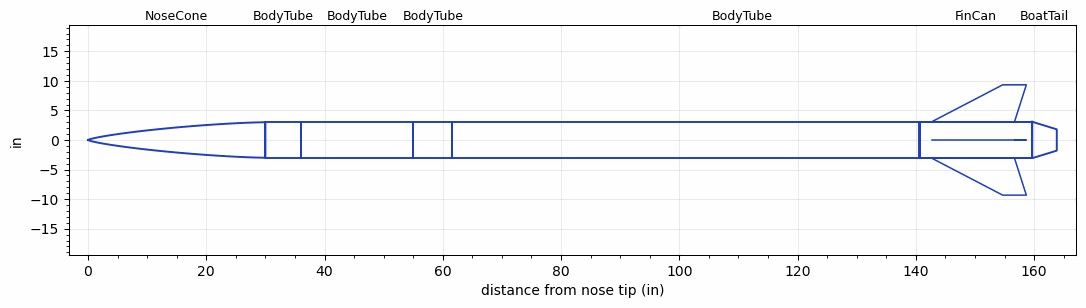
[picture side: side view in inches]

<RASAeroDocument>
 <FileVersion>2</FileVersion>
 <RocketDesign>
  <NoseCone>
   <Length>29.9999</Length>
   <Diameter>6</Diameter>
   <Shape>Von Karman Ogive</Shape>
   <Location>0</Location>
  </NoseCone>
  <BodyTube>
   <Length>6</Length>
   <Diameter>6</Diameter>
   <Location>29.9999</Location>
  </BodyTube>
  <BodyTube>
   <Length>19</Length>
   <Diameter>6</Diameter>
   <Location>35.9999</Location>
  </BodyTube>
  <BodyTube>
   <Length>6.628</Length>
   <Diameter>6</Diameter>
   <Location>54.9999</Location>
  </BodyTube>
  <BodyTube>
   <Length>98.0598</Length>
   <Diameter>6</Diameter>
   <Location>61.6279</Location>
  </BodyTube>
  <FinCan>
   <Length>19</Length>
   <Diameter>6.154</Diameter>
   <InsideDiameter>6</InsideDiameter>
   <Location>159.6877</Location>
   <ShoulderLength>0.1333</ShoulderLength>
   <Offset>-19</Offset>
   <Fin>
    <Count>4</Count>
    <Chord>14</Chord>
    <Span>6.25</Span>
    <SweepDistance>12</SweepDistance>
    <TipChord>4</TipChord>
    <Thickness>0.3</Thickness>
    <LERadius>0.0313</LERadius>
    <Location>17</Location>
    <AirfoilSection>Double Wedge</AirfoilSection>
    <FX1>3.9</FX1>
    <FX3>3.9</FX3>
   </Fin>
  </FinCan>
  <BoatTail>
   <Length>4.15</Length>
   <Diameter>6.154</Diameter>
   <RearDiameter>3.6</RearDiameter>
   <Location>159.6877</Location>
  </BoatTail>
  <Surface>Rough Camouflage Paint</Surface>
  <ModifiedBarrowman>True</ModifiedBarrowman>
  <Turbulence>True</Turbulence>
  <UseBooster1>False</UseBooster1>
  <UseBooster2>False</UseBooster2>
  <Comments>2027 IREC Rocket Design</Comments>
 </RocketDesign>
 <LaunchSite>
  <Altitude>2800</Altitude>
  <Pressure>26.96</Pressure>
  <RodAngle>4</RodAngle>
  <RodLength>32.8</RodLength>
  <Temperature>92.19</Temperature>
  <WindSpeed>18</WindSpeed>
 </LaunchSite>
 <Recovery>
  <Altitude1>0</Altitude1>
  <Altitude2>0</Altitude2>
  <DeviceType1>None</DeviceType1>
  <DeviceType2>None</DeviceType2>
  <Event1>False</Event1>
  <Event2>False</Event2>
  <Size1>0</Size1>
  <Size2>0</Size2>
  <EventType1>None</EventType1>
  <EventType2>None</EventType2>
  <CD1>0</CD1>
  <CD2>0</CD2>
 </Recovery>
 <SimulationList>
  <Simulation>
   <SustainerEngine>PER_MY_LAST-eng  (TAMUSRT)</SustainerEngine>
   <SustainerLaunchWt>135.73</SustainerLaunchWt>
   <SustainerCG>93.72</SustainerCG>
   <SustainerIgnitionDelay>0</SustainerIgnitionDelay>
   <Booster1SeparationDelay>0</Booster1SeparationDelay>
   <Booster1IgnitionDelay>0</Booster1IgnitionDelay>
   <IncludeBooster1>False</IncludeBooster1>
   <Booster2Delay>0</Booster2Delay>
   <IncludeBooster2>False</IncludeBooster2>
   <TimetoApogee>45.50837</TimetoApogee>
   <MaxAltitude>33133.25</MaxAltitude>
   <MaxVelocity>1745.228</MaxVelocity>
  </Simulation>
  <Simulation>
   <SustainerLaunchWt>135.7287</SustainerLaunchWt>
   <SustainerCG>93.7201</SustainerCG>
   <SustainerIgnitionDelay>0</SustainerIgnitionDelay>
   <Booster1SeparationDelay>0</Booster1SeparationDelay>
   <Booster1IgnitionDelay>0</Booster1IgnitionDelay>
   <IncludeBooster1>False</IncludeBooster1>
   <Booster2Delay>0</Booster2Delay>
   <IncludeBooster2>False</IncludeBooster2>
  </Simulation>
  <Simulation>
   <SustainerLaunchWt>135.7287</SustainerLaunchWt>
   <SustainerCG>93.7201</SustainerCG>
   <SustainerIgnitionDelay>0</SustainerIgnitionDelay>
   <Booster1SeparationDelay>0</Booster1SeparationDelay>
   <Booster1IgnitionDelay>0</Booster1IgnitionDelay>
   <IncludeBooster1>False</IncludeBooster1>
   <Booster2Delay>0</Booster2Delay>
   <IncludeBooster2>False</IncludeBooster2>
  </Simulation>
 </SimulationList>
</RASAeroDocument>
